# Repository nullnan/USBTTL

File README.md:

# USBTTL
A simple USB to TTL module. Made with `ft231xq` chip.
   
**No actual testing or simulation has been performed. And it has bad wiring I think.**

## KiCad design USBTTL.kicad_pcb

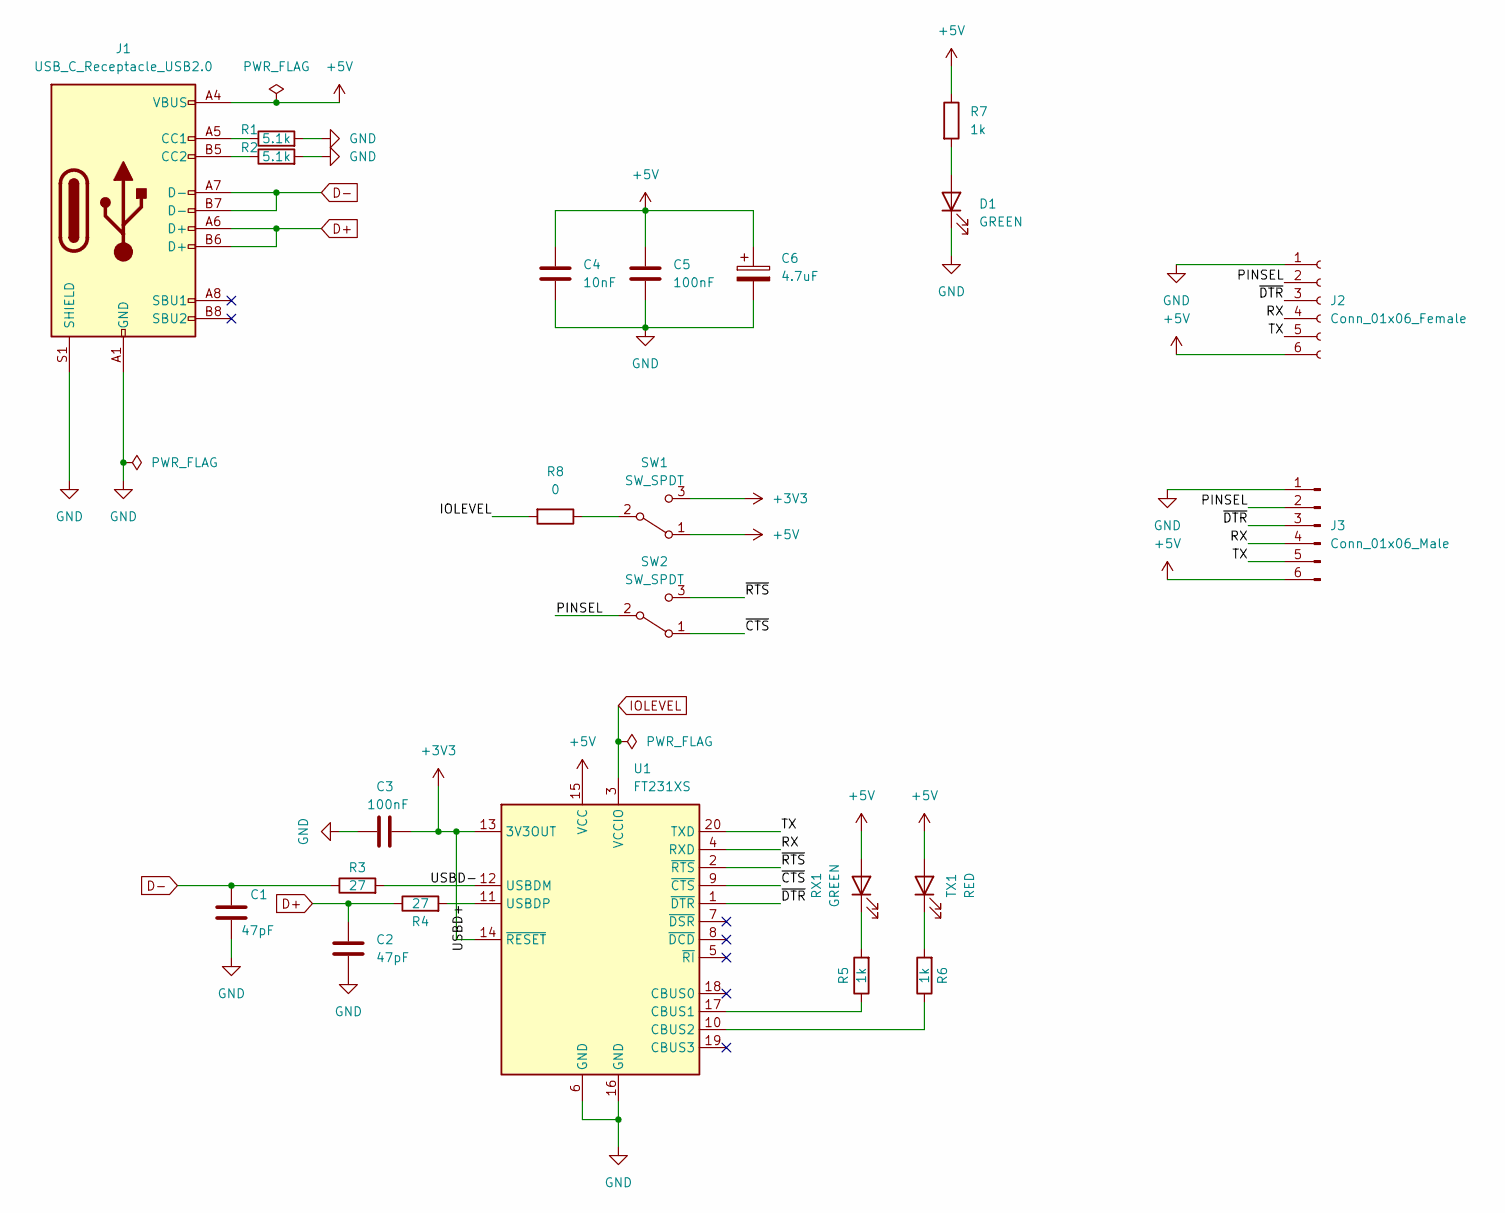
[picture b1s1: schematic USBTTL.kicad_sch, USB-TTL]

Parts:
C1, C2: 47pF; C_0603_1608Metric_Pad1.08x0.95mm_HandSolder
C3, C5: 100nF; C_0603_1608Metric_Pad1.08x0.95mm_HandSolder
C4: 10nF; C_0603_1608Metric_Pad1.08x0.95mm_HandSolder
C6: 4.7uF; C_0603_1608Metric_Pad1.08x0.95mm_HandSolder
D1: GREEN; LED_0603_1608Metric_Pad1.05x0.95mm_HandSolder
J1: USB_C_Receptacle_USB2.0; USB_C_Receptacle_Palconn_UTC16-G
J2: Conn_01x06_Female; PinSocket_1x06_P2.54mm_Vertical
J3: Conn_01x06_Male; PinHeader_1x06_P2.54mm_Horizontal
R1, R2: 5.1k; R_0603_1608Metric_Pad0.98x0.95mm_HandSolder
R3, R4: 27; R_0603_1608Metric_Pad0.98x0.95mm_HandSolder
R5, R6, R7: 1k; R_0603_1608Metric_Pad0.98x0.95mm_HandSolder
R8: 0; R_0603_1608Metric_Pad0.98x0.95mm_HandSolder
RX1: GREEN; LED_0603_1608Metric_Pad1.05x0.95mm_HandSolder
SW1, SW2: SW_SPDT; SW_SPDT_PCM12
TX1: RED; LED_0603_1608Metric_Pad1.05x0.95mm_HandSolder
U1: FT231XS; SSOP-20_3.9x8.7mm_P0.635mm

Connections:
+3V3: C3.1, SW1.3 (C), U1.13 (3V3OUT), U1.14 (~RESET)
+5V: C4.1, C5.1, C6.1, J1.A4 (VBUS), J1.A9 (VBUS), J1.B4 (VBUS), J1.B9 (VBUS), J2.6, J3.6, R7.1, RX1.2 (A), SW1.1 (A), TX1.2 (A), U1.15 (VCC)
/PINSEL: J2.2, J3.2, SW2.2 (B)
/RX: J2.4, J3.4, U1.4 (RXD)
/TX: J2.5, J3.5, U1.20 (TXD)
/USBD+: R4.2, U1.11 (USBDP)
/USBD-: R3.2, U1.12 (USBDM)
/~CTS: SW2.1 (A), U1.9 (~CTS)
/~DTR: J2.3, J3.3, U1.1 (~DTR)
/~RTS: SW2.3 (C), U1.2 (~RTS)
D+: C2.1, J1.A6 (D+), J1.B6 (D+), R4.1
D-: C1.1, J1.A7 (D-), J1.B7 (D-), R3.1
GND: C1.2, C2.2, C3.2, C4.2, C5.2, C6.2, D1.1 (K), J1.A1 (GND), J1.A12 (GND), J1.B1 (GND), J1.B12 (GND), J1.S1 (SHIELD), J2.1, J3.1, R1.2, R2.2, U1.6 (GND), U1.16 (GND)
IOLEVEL: R8.2, U1.3 (VCCIO)
unnamed: D1.2 (A), R7.2
unnamed: J1.A5 (CC1), R1.1
unnamed: J1.B5 (CC2), R2.1
unnamed: R5.1, U1.17 (CBUS1)
unnamed: R5.2, RX1.1 (K)
unnamed: R6.1, U1.10 (CBUS2)
unnamed: R6.2, TX1.1 (K)
unnamed: R8.1, SW1.2 (B)

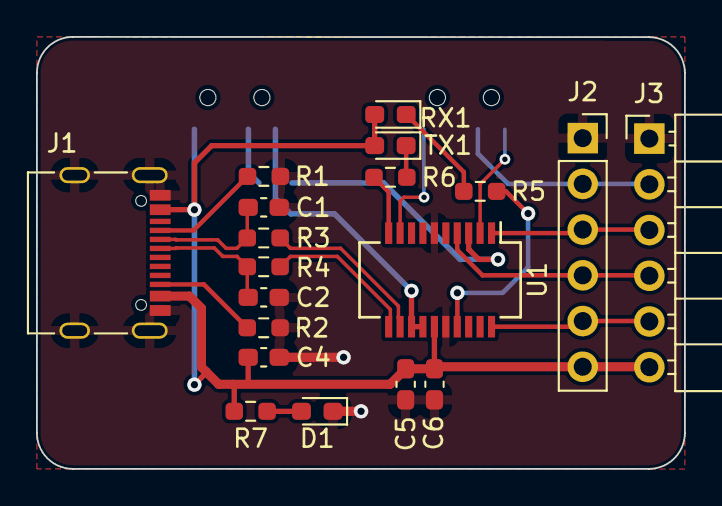
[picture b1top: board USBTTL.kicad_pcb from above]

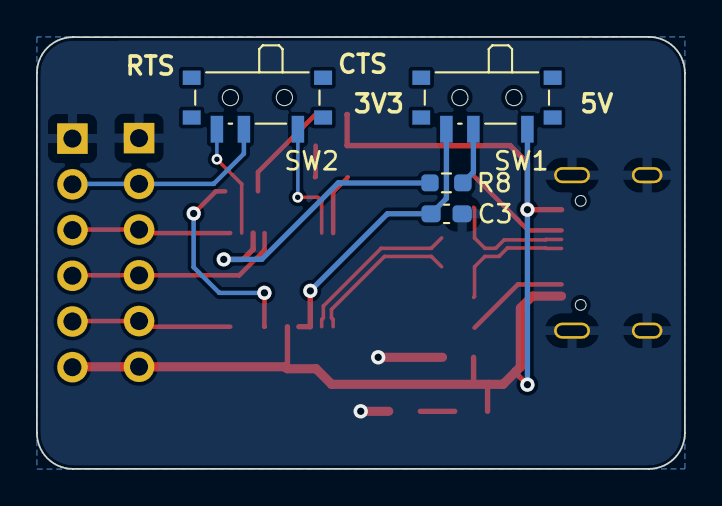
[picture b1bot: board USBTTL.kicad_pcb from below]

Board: 2 copper layers, 36.0 x 24.0 mm, 23 parts (4 on the bottom side), 22 nets.

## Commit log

2022-08-07 Finish wiring.
